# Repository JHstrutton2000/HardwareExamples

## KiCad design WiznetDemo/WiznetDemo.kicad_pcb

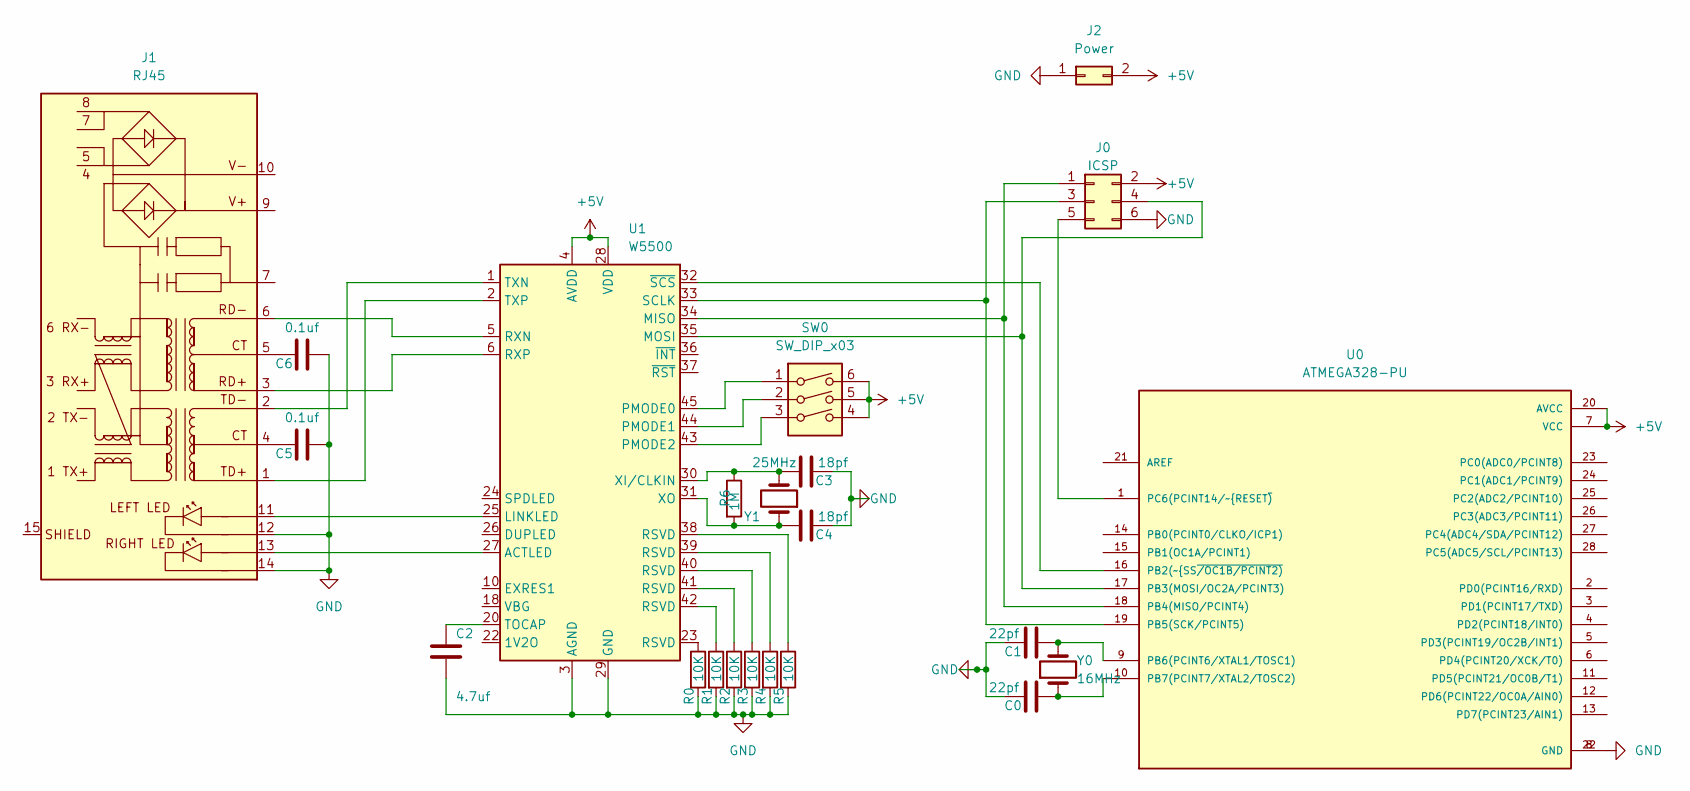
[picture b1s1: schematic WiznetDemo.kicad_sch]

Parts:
C0, C1: 22pf; CAPC3216X94N
C2: 4.7uf; CAPC3216X94N
C3, C4: 18pf; CAPC3216X94N
C5, C6: 0.1uf; CAPC3216X94N
J0: ICSP; PinHeader_2x03_P2.54mm_Vertical
J1: RJ45; RJ45_Abracon_ARJP11A-MA_Horizontal
J2: Power; PinHeader_2x01_P2.54mm_Vertical
R0, R1, R2, R3, R4, R5: 10K; R_Axial_DIN0204_L3.6mm_D1.6mm_P7.62mm_Horizontal
R6: 1M; R_Axial_DIN0204_L3.6mm_D1.6mm_P7.62mm_Horizontal
SW0: SW_DIP_x03; SW_A6SN-3101
U0: ATMEGA328-PU; DIP787W46P254L3467H508Q28; PARTREV B
U1: W5500; LQFP-48_7x7mm_P0.5mm
Y0: 16MHz; Crystal_HC18-U_Vertical
Y1: 25MHz; Crystal_HC18-U_Vertical

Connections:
+5V: J0.2, J2.2, SW0.4, SW0.5, SW0.6, U0.7 (VCC), U0.20 (AVCC), U1.4 (AVDD), U1.8 (AVDD), U1.11 (AVDD), U1.15 (AVDD), U1.17 (AVDD), U1.21 (AVDD), U1.28 (VDD)
GND: C0.1, C1.1, C2.2, C3.1, C4.1, C5.1, C6.1, J0.6, J1.12 (LLED-), J1.14 (RLED-), J2.1, R0.2, R1.2, R2.2, R3.2, R4.2, R5.2, U0.8 (GND), U0.22 (GND), U1.3 (AGND), U1.9 (AGND), U1.14 (AGND), U1.16 (AGND), U1.19 (AGND), U1.29 (GND), U1.48 (AGND)
unnamed: C0.2, U0.10 (PB7(PCINT7/XTAL2/TOSC2)), Y0.1
unnamed: C1.2, U0.9 (PB6(PCINT6/XTAL1/TOSC1)), Y0.2
unnamed: C2.1, U1.20 (TOCAP)
unnamed: C4.2, R6.2, U1.31 (XO), Y1.1
unnamed: C5.2, J1.4 (CT)
unnamed: C6.2, J1.5 (CT)
unnamed: J0.1, U0.18 (PB4(MISO/PCINT4)), U1.34 (MISO)
unnamed: J0.3, U0.19 (PB5(SCK/PCINT5)), U1.33 (SCLK)
unnamed: J0.4, U0.17 (PB3(MOSI/OC2A/PCINT3)), U1.35 (MOSI)
unnamed: J0.5, U0.1 (PC6(PCINT14/~RESET~{))
unnamed: J1.1 (TD+), U1.2 (TXP)
unnamed: J1.2 (TD-), U1.1 (TXN)
unnamed: J1.3 (RD+), U1.6 (RXP)
unnamed: J1.6 (RD-), U1.5 (RXN)
unnamed: J1.11 (LLED+), U1.25 (LINKLED)
unnamed: J1.13 (RLED+), U1.27 (ACTLED)
unnamed: R0.1, U1.23 (RSVD)
unnamed: R1.1, U1.42 (RSVD)
unnamed: R2.1, U1.41 (RSVD)
unnamed: R3.1, U1.40 (RSVD)
unnamed: R4.1, U1.39 (RSVD)
unnamed: R5.1, U1.38 (RSVD)
unnamed: C3.2, R6.1, U1.30 (XI/CLKIN), Y1.2
unnamed: SW0.1, U1.45 (PMODE0)
unnamed: SW0.2, U1.44 (PMODE1)
unnamed: SW0.3, U1.43 (PMODE2)
unnamed: U0.16 (PB2(~SS~{/OC1B/PCINT2)), U1.32 (~SCS)

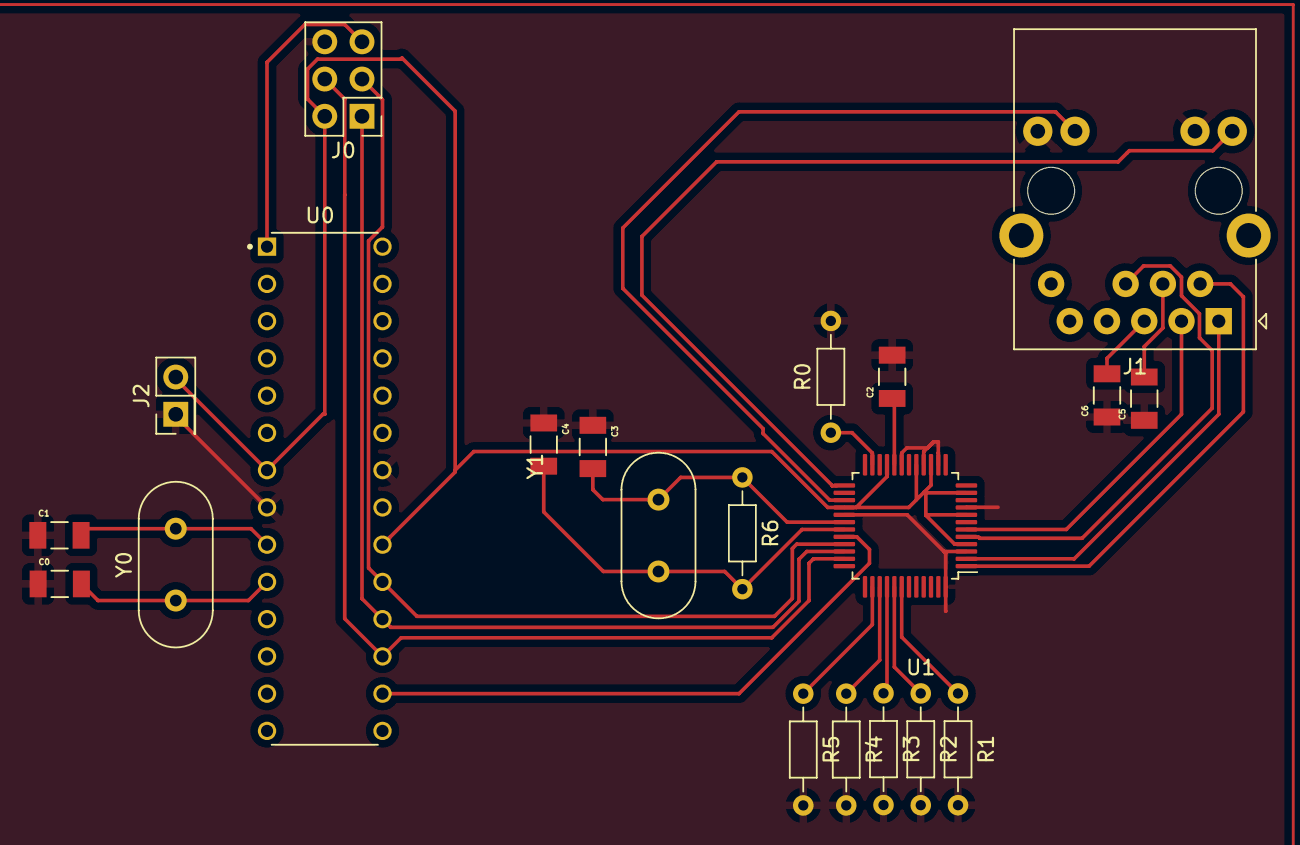
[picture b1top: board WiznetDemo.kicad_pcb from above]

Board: 2 copper layers, 21 parts (0 on the bottom side), 26 nets.

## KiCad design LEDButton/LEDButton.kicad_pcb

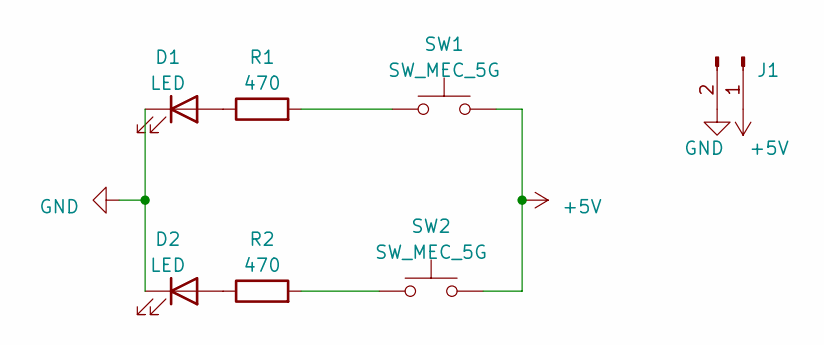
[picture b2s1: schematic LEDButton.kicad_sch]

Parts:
D1, D2: LED; LED_D3.0mm
J1: Conn_01x02_Pin; AMASS_XT30U-M_1x02_P5.0mm_Vertical
R1, R2: 470; R_Axial_DIN0614_L14.3mm_D5.7mm_P25.40mm_Horizontal
SW1, SW2: SW_MEC_5G; SW_MEC_5GSH9

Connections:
+5V: J1.1, SW1.3 (B), SW1.4 (B), SW2.3 (B), SW2.4 (B)
GND: D1.1 (K), D2.1 (K), J1.2
unnamed: D1.2 (A), R1.1
unnamed: D2.2 (A), R2.1
unnamed: R1.2, SW1.1 (A), SW1.2 (A)
unnamed: R2.2, SW2.1 (A), SW2.2 (A)

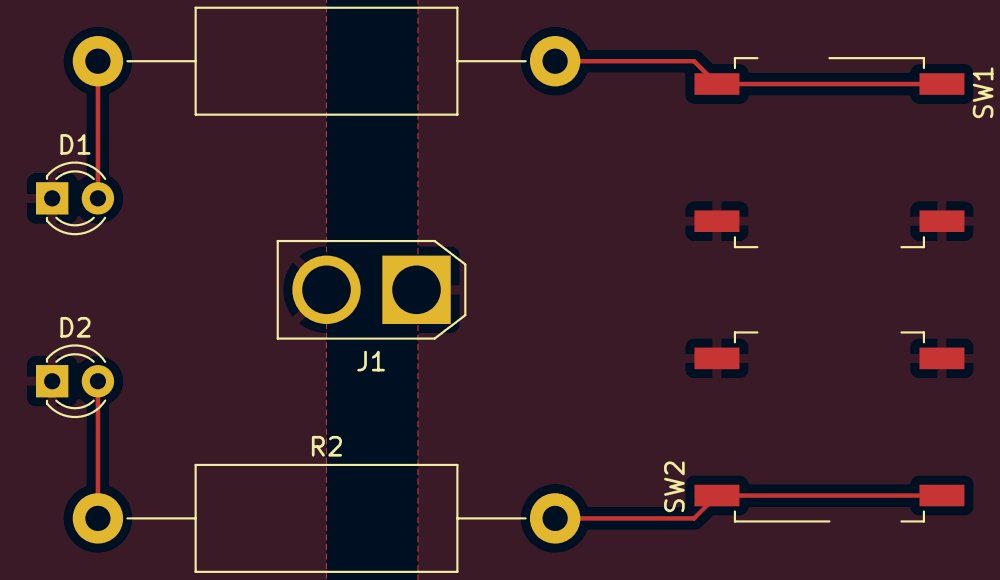
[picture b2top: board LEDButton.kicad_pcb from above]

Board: 2 copper layers, 7 parts (0 on the bottom side), 6 nets.

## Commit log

2023-11-09 Commited HardwareExamples
2023-11-09 Commited 555FrequencyGen
